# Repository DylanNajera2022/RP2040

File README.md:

# RP2040
It's a simple RP2040 board that I created. Initially, I was only going to add one sensor because if I wanted to add the ones I had originally planned, I would have had to pay for the standard assembly mode on JLCPBC, and that is three times more expensive. But I looked for alternatives to the sensors I wanted and ended up adding, in the end, the SHTC3, SGP40, LTR-390, and as a bonus, an addressable RGB LED. In the future, with what I've learned, I plan to make an improved board that includes battery operation or some module like LoRa or something similar.

# Schematic and PCB:
Due to the experience I gained previously with my Macropad, it was much easier for me to make the schematic and the PCB, but I did go through many iterations until I found one that I liked.

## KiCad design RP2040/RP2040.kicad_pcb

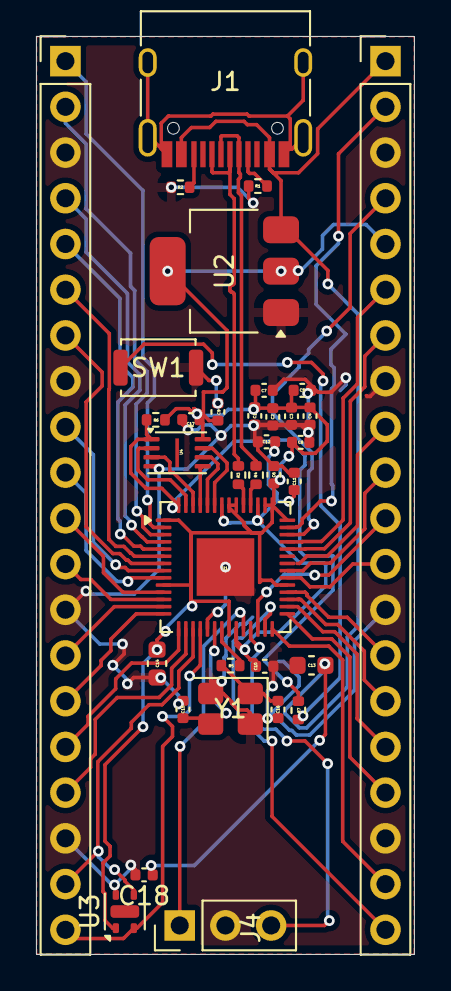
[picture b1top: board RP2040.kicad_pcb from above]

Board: 2 copper layers, 21.0 x 51.0 mm, 35 parts (0 on the bottom side), 53 nets.

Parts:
C1, C10: 1uF; C_0402_1005Metric
C2, C3, C4, C5, C6, C7, C8, C9, C11, C12, C17: 0.1uF; C_0402_1005Metric
C13, C14: 10uF; C_0603_1608Metric
C15, C16: 33pF; C_0402_1005Metric
C18: 47 µF; C_0402_1005Metric
J1: USB_C_Receptacle_USB2.0_14P; USB_C_Receptacle_HRO_TYPE-C-31-M-12
J2, J3: Conn_01x20; PinHeader_1x20_P2.54mm_Vertical
J4: Conn_01x03; PinHeader_1x03_P2.54mm_Vertical
R1, R2: 5.1K; R_0402_1005Metric
R3, R4: 27; R_0402_1005Metric
R5, R7: 1K; R_0402_1005Metric
R6: 10K; R_0402_1005Metric
SW1: SW_Push; SW_Push_SPST_NO_Alps_SKRK
U1: RP2040; QFN-56-1EP_7x7mm_P0.4mm_EP3.2x3.2mm
U2: NCP1117-3.3_SOT223; SOT-223-3_TabPin2
U3: SHTC3; Sensirion_DFN-4-1EP_2x2mm_P1mm_EP0.7x1.6mm
U4: W25Q16JVSS; Winbond_USON-8-1EP_3x2mm_P0.5mm_EP0.2x1.6mm
Y1: 12 MHz; Crystal_SMD_3225-4Pin_3.2x2.5mm

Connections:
+1V1: C10.1, C11.1, C12.1, U1.23 (DVDD), U1.45 (VREG_VOUT), U1.50 (DVDD)
+3V3: C1.1, C2.1, C3.1, C4.1, C5.1, C6.1, C7.1, C8.1, C9.1, C14.1, C17.1, J3.5, R6.1, U1.1 (IOVDD), U1.10 (IOVDD), U1.22 (IOVDD), U1.33 (IOVDD), U1.42 (IOVDD), U1.43 (ADC_AVDD), U1.44 (VREG_IN), U1.48 (USB_VDD), U1.49 (IOVDD), U2.2 (VO), U3.1 (VDD), U4.8 (VCC)
GND: C1.2, C2.2, C3.2, C4.2, C5.2, C6.2, C7.2, C8.2, C9.2, C10.2, C11.2, C12.2, C13.2, C14.2, C15.1, C16.1, C17.2, C18.2, J2.3, J2.8, J2.13, J2.18, J3.3, J3.8, J3.13, J3.18, J4.2, R1.2, R2.2, SW1.1, U1.19 (TESTEN), U1.57 (GND), U2.1 (GND), U3.4 (VSS), U4.4 (GND), Y1.2, Y1.4
GPIO0: J2.1, U1.2 (GPIO0)
GPIO1: J2.2, U1.3 (GPIO1)
GPIO2: J2.4, U1.4 (GPIO2)
GPIO3: J2.5, U1.5 (GPIO3)
GPIO4: J2.6, U1.6 (GPIO4)
GPIO5: J2.7, U1.7 (GPIO5)
GPIO6: J2.9, U1.8 (GPIO6)
GPIO7: J2.10, U1.9 (GPIO7)
GPIO8: J2.11, U1.11 (GPIO8)
GPIO9: J2.12, U1.12 (GPIO9)
GPIO10: J2.14, U1.13 (GPIO10)
GPIO11: J2.15, U1.14 (GPIO11)
GPIO12: J2.16, U1.15 (GPIO12)
GPIO13: J2.17, U1.16 (GPIO13)
GPIO14: J2.19, U1.17 (GPIO14), U3.3 (SDA)
GPIO15: J2.20, U1.18 (GPIO15), U3.2 (SCL)
GPIO16: J3.20, U1.27 (GPIO16)
GPIO17: J3.19, U1.28 (GPIO17)
GPIO18: J3.17, U1.29 (GPIO18)
GPIO19: J3.16, U1.30 (GPIO19)
GPIO20: J3.15, U1.31 (GPIO20)
GPIO21: J3.14, U1.32 (GPIO21)
GPIO22: J3.12, U1.34 (GPIO22)
GPIO23: J3.10, U1.35 (GPIO23)
GPIO24: J3.9, U1.36 (GPIO24)
GPIO26_ADC0: J3.7, U1.38 (GPIO26_ADC0)
GPIO27_ADC1: J3.6, U1.39 (GPIO27_ADC1)
GPIO28_ADC2: J3.4, U1.40 (GPIO28_ADC2)
GPIO29_ADC3: J3.2, U1.41 (GPIO29_ADC3)
unnamed: C16.2, R5.1, Y1.1
unnamed: J1.A5 (CC1), R1.1
unnamed: J1.B5 (CC2), R2.1
unnamed: J1.A1 (GND), J1.A12 (GND), J1.B1 (GND), J1.B12 (GND), J1.S1 (SHIELD)
unnamed: R7.1, SW1.2
unnamed: R4.2, U1.46 (USB_DM)
unnamed: R3.1, U1.47 (USB_DP)
QSPI_SCLK: U1.52 (QSPI_SCLK), U4.6 (CLK)
QSPI_SD0: U1.53 (QSPI_SD0), U4.5 (DI/IO_{0})
QSPI_SD1: U1.55 (QSPI_SD1), U4.2 (DO/IO_{1})
QSPI_SD2: U1.54 (QSPI_SD2), U4.3 (~WP/IO_{2})
QSPI_SD3: U1.51 (QSPI_SD3), U4.7 (~HOLD/~RESET/IO_{3})
QSPI_SS: R6.2, R7.2, U1.56 (QSPI_SS), U4.1 (~CS)
RUN: J3.11, U1.26 (RUN)
SWCLK: J4.1, U1.24 (SWCLK)
SWD: J4.3, U1.25 (SWD)
USBD+: J1.A6 (D+), J1.B6 (D+), R3.2
USBD-: J1.A7 (D-), J1.B7 (D-), R4.1
VBUS: C13.1, C18.1, J1.A4 (VBUS), J1.A9 (VBUS), J1.B4 (VBUS), J1.B9 (VBUS), J3.1, U2.3 (VI)
XIN: C15.2, U1.20 (XIN), Y1.3
XOUT: R5.2, U1.21 (XOUT)

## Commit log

2026-01-01 Enhance README with project details and images
    Expanded description of the RP2040 project, including future plans and schematic/PCB details.
2026-01-11 Add new image to README
2026-01-11 Update README with detailed board description and images
    Expanded description of the RP2040 board and added additional sensor details. Included new images to enhance documentation.
